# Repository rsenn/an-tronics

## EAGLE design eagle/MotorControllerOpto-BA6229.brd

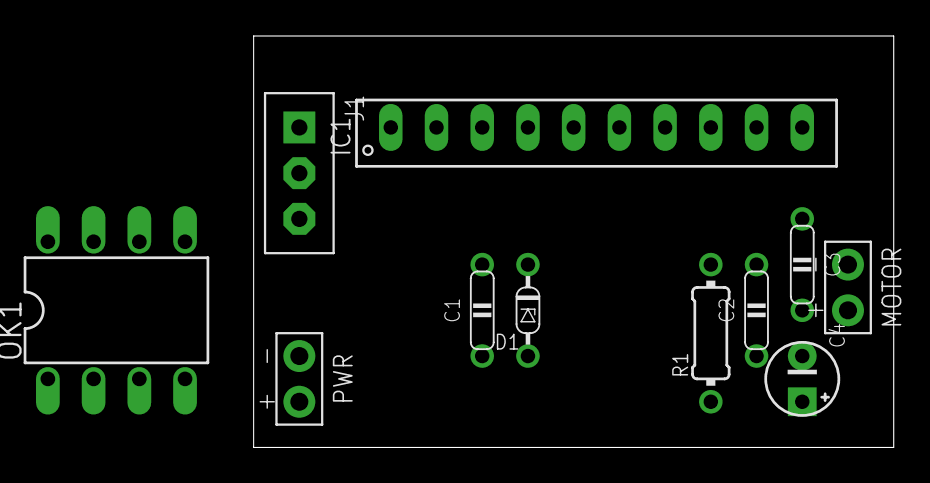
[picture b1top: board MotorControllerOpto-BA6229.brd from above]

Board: 2 copper layers, 35.6 x 22.9 mm, 11 parts (0 on the bottom side), 10 nets, no tracks yet.

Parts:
C1, C2: 0.1μF; C050-020X044
C3: 0.33μF; C050-020X044
C4: 100μF; E2,5-4
D1: Z=4.7V; DO34Z5V
IC1: BA6229; SIL10
J1: CONN-3P-3P; CONN-3P
MOTOR: SPAD+-
OK1: HCPL2730; DIL08
PWR: SPAD+-
R1: 10Ω; 0204/7-V

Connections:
GND: C1.2, C2.2, C4.-, D1.A, IC1.1, J1.1, PWR.1
unnamed: C3.1, IC1.2, MOTOR.2
unnamed: C2.1, IC1.9
unnamed: C1.1, IC1.3
unnamed: D1.C, IC1.4
unnamed: IC1.5, J1.2
unnamed: C3.2, IC1.10, MOTOR.1
unnamed: IC1.6, J1.3
unnamed: IC1.8, R1.1
VCC: C4.+, IC1.7, PWR.2, R1.2

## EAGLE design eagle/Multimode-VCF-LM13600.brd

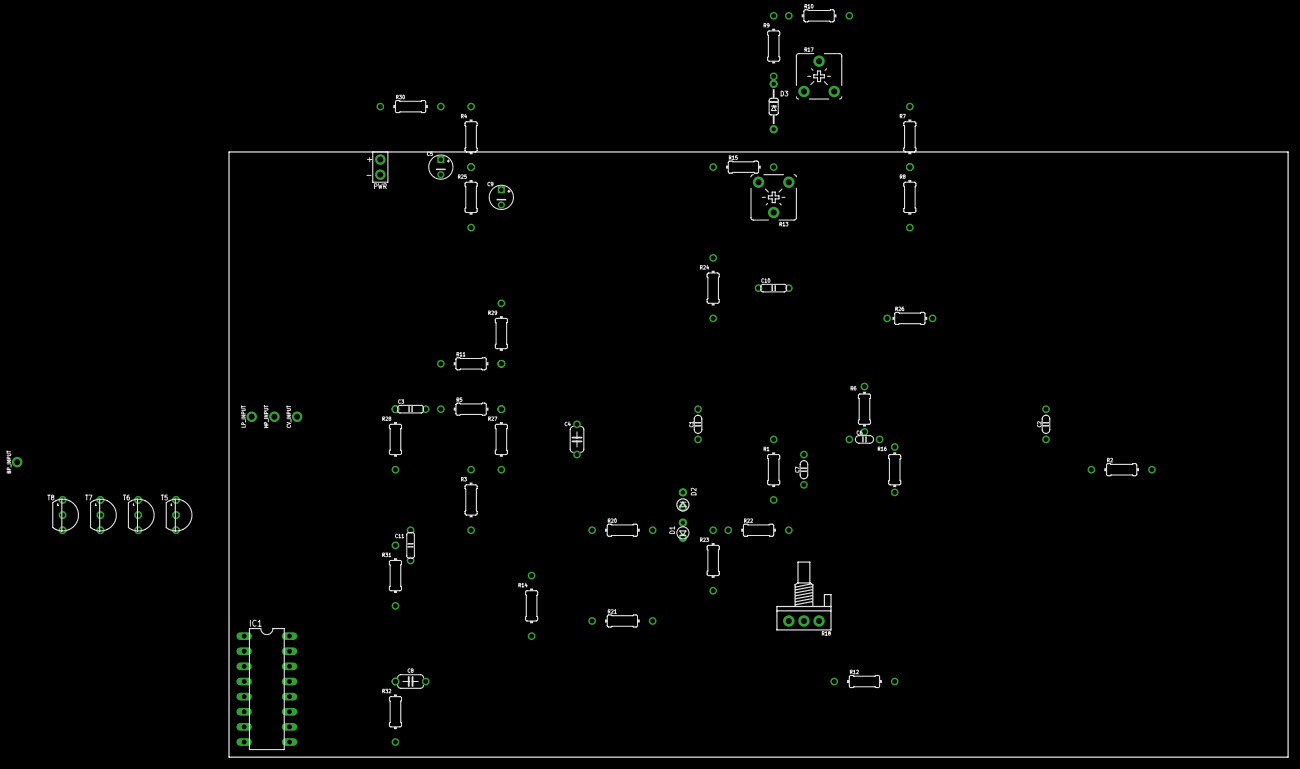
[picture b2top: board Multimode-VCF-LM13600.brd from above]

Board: 2 copper layers, 177.8 x 101.6 mm, 55 parts (0 on the bottom side), 34 nets, no tracks yet.

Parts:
BP_INPUT: SPAD
C1, C2: 220pF; C050-020X036/V
C3, C10: 100nF; C050-020X044
C4: 2.2uF; C050-024X044/V
C5: 33uF; E2.5-4/V
C6: 10pF; C050-020X036
C7: 10uF; C050-020X036/V
C8: 1uF; C050-024X044
C9: 100uF; E2.5-4/V
C11: 100nF; C050-020X044/V
CV_INPUT: SPAD
D1: 1N4148; DO34-2,5-A
D2: 1N4148; DO34-2,5
D3: Z=5.6V/1W; DO35Z7/V
HP_INPUT: SPAD
IC1: LM13600; DIL16
LP_INPUT: SPAD
PWR: SPAD+--+; SPAD-+
R1, R9, R25: 10k; 0204/10-V
R2: 10k; 0204/10
R3, R24: 220k; 0204/10-V
R4: 13k; 0204/10-V
R5: 150k; 0204/10
R6: 100k; 0204/7-V
R7: 18k; 0204/10-V
R8, R14: 22k; 0204/10-V
R10: 4.7k; 0204/10
R11, R12, R15: 100k; 0204/10
R13, R17: 2M; POT-V
R16: 1k; 0204/7-V
R18: 100k; POT
R20: 22k; 0204/10
R21: 30k; 0204/10
R22: 68k; 0204/10
R23, R28, R31, R32: 100k; 0204/10-V
R26: 1k; 0204/7
R27, R29: 1k; 0204/10-V
R30: 100; 0204/10
T5, T6, T7, T8: 2N3904; TO92

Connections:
BIAS: C9.+, R3.1, R4.2, R16.1, R25.1, R26.2, R27.2, R29.1
GND: C2.2, C5.-, C9.-, D3.A, IC1.6, PWR.1, R1.2, R2.1, R8.2, R13.E, R14.2, R18.3, R23.2, R25.2, R28.2, R31.2, R32.2
unnamed: C4.2, R20.1, R21.1
unnamed: IC1.3, R5.2, R24.1, R27.1
unnamed: C1.2, R14.1, T8.1
unnamed: C11.2, R3.2, T8.2
unnamed: C1.1, IC1.5, IC1.7
unnamed: C6.1, C7.1, C10.2, IC1.8, R1.1, R6.1
unnamed: D1.C, D2.A, R20.2
unnamed: D1.A, D2.C, R22.1, R23.1
unnamed: C10.1, R24.2
unnamed: C6.2, IC1.14, R6.2, R16.2
unnamed: R18.2, R21.2
unnamed: C7.2, R18.1, R22.2
unnamed: C4.1, IC1.4, R11.2, R29.2
unnamed: IC1.13, R12.2, R26.1
unnamed: C8.2, R12.1
unnamed: C8.1, LP_INPUT.1, R32.1
unnamed: C11.1, HP_INPUT.1, R31.1
unnamed: C3.2, R5.1
unnamed: BP_INPUT.1, C3.1, R28.1
unnamed: C2.1, IC1.9, IC1.12
unnamed: IC1.10, R2.2, R11.1
unnamed: R17.A, T5.3, T7.2
unnamed: T6.2, T7.1
unnamed: IC1.1, IC1.16, R7.1, T6.1
unnamed: R7.2, R8.1, T5.2
unnamed: D3.C, R9.2, R17.S
unnamed: R10.2, T6.3, T7.3
unnamed: R13.S, T5.1
unnamed: CV_INPUT.1, R15.1
unnamed: R13.A, R15.2
unnamed: PWR.2, R30.1
VCC: C5.+, IC1.11, R4.1, R9.1, R10.1, R30.2, T8.3

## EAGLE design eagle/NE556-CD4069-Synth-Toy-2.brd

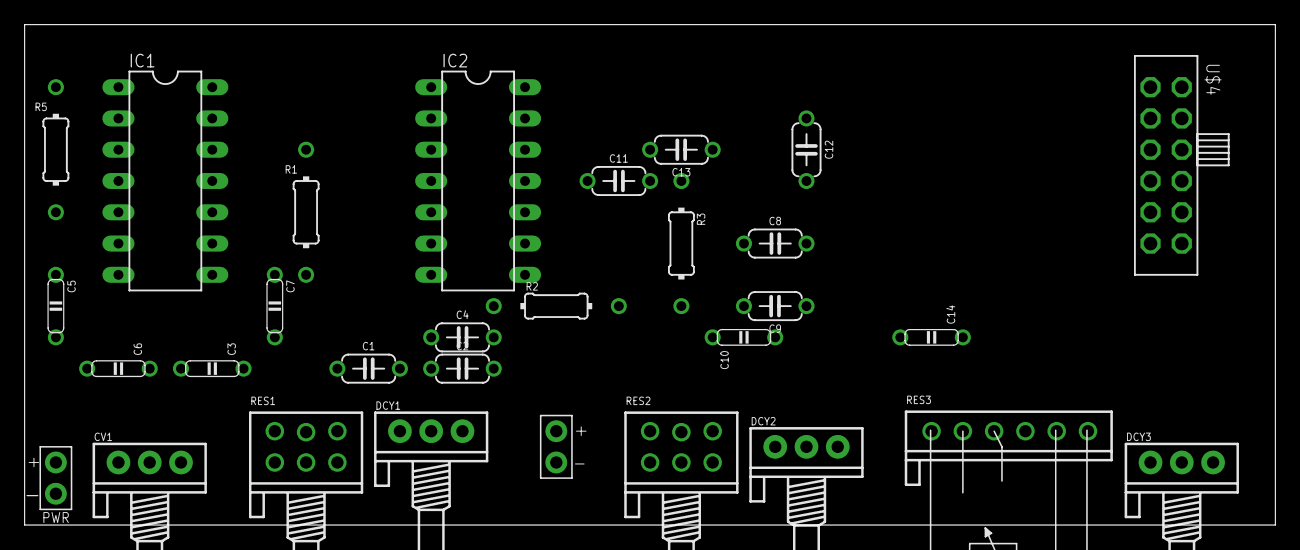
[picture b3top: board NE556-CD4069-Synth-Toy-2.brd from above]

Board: 2 copper layers, 101.6 x 40.6 mm, 30 parts (0 on the bottom side), 22 nets, no tracks yet.

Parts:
C1, C2: 100nF; C050-024X044
C3: 220nF; C050-020X044/V
C4, C11: 470nF; C050-024X044
C5, C7: 100nF; C050-020X044
C6: 10nF; C050-020X044/V
C8, C9: 330nF; C050-024X044
C10, C14: 470nF; C050-020X044/V
C12, C13: 68nF; C050-024X044
CV1: 20kΩ; POT
DCY1, DCY2, DCY3: 20kΩ; POT
IC1: LM556N; DIL14
IC2: 4069N; DIL14
OUT: SPAD+-
R1, R5: 33kΩ; 0204/10-V
R2, R3: R-H0204/10; 0204/10
RES1, RES2: 100kΩ; POT-STEREO-2X3
RES3: 100kΩ; POT-STEREO-1X6-V
S3: VCC_GNDPWR-L; PWR-L
U$4: SL-SW-2P-4T; SLSW-2P4T-2-H

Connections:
GND: C3.2, C5.2, C6.2, C7.2, C10.2, C14.2, CV1.E, DCY1.A, DCY2.A, DCY3.A, IC1.7, IC2.7, OUT.1, S3.1
unnamed: C2.2, IC2.3, IC2.6, RES1.1-E, RES1.1-S
unnamed: IC1.5, R5.2, U$4.A2
unnamed: C4.2, R2.1
unnamed: C3.1, RES1.1-A, RES1.2-E, RES1.2-S
unnamed: C14.1, RES3.1A, RES3.2E, RES3.2S
unnamed: C4.1, IC2.4
unnamed: C1.1, IC2.5, RES1.2-A
unnamed: C5.1, IC1.2, IC1.6, R5.1
unnamed: C6.1, CV1.S, IC1.3, IC1.11
unnamed: C12.1, IC2.13, RES3.2A
unnamed: IC1.9, R1.1, U$4.A3
unnamed: C7.1, IC1.8, IC1.12, R1.2
unnamed: C10.1, RES2.1-A, RES2.2-E, RES2.2-S
unnamed: C8.1, IC2.9, RES2.2-A
unnamed: C13.2, IC2.1, IC2.12, RES3.1E, RES3.1S
unnamed: C11.2, R3.1
unnamed: C11.1, IC2.10
unnamed: OUT.2, R2.2, R3.2
unnamed: C9.2, IC2.8, IC2.11, RES2.1-E, RES2.1-S
TRIG1: C1.2, C2.1, C8.2, C9.1, C12.2, C13.1, DCY1.E, DCY1.S, DCY2.E, DCY2.S, DCY3.E, DCY3.S, U$4.A1, U$4.A6
VCC: CV1.A, IC1.4, IC1.10, IC1.14, IC2.14, S3.2

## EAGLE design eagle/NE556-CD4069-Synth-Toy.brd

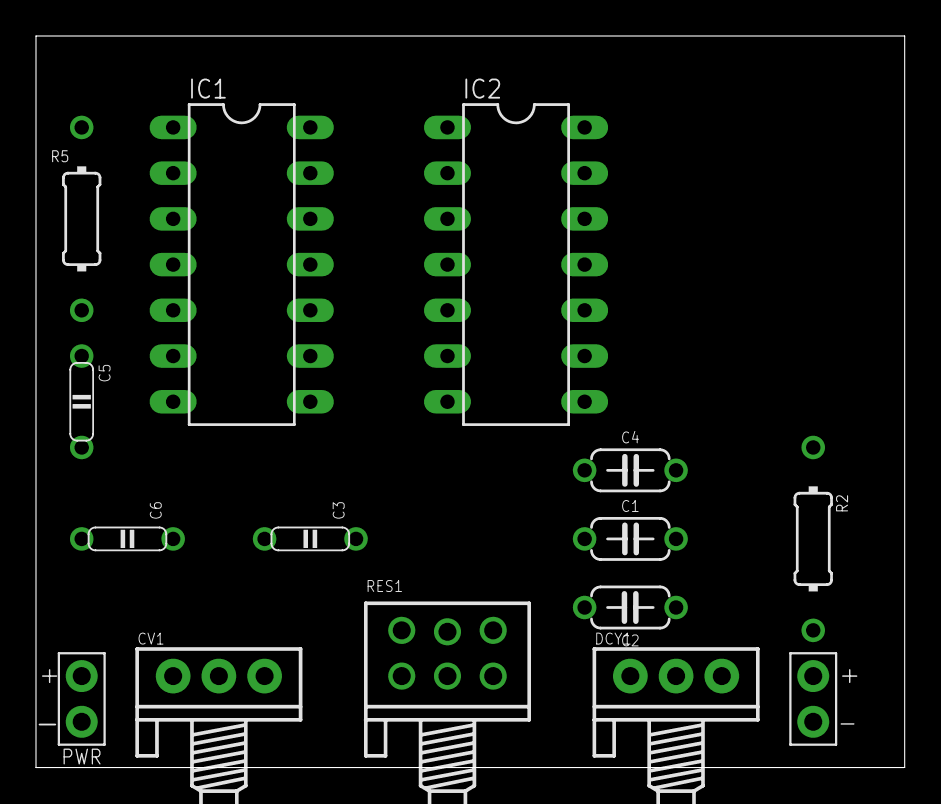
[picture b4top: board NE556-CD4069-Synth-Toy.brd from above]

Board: 2 copper layers, 48.3 x 40.6 mm, 15 parts (0 on the bottom side), 12 nets, no tracks yet.

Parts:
C1, C2: 100nF; C050-024X044
C3: 220nF; C050-020X044/V
C4: 470nF; C050-024X044
C5: 100nF; C050-020X044
C6: 10nF; C050-020X044/V
CV1: 20kΩ; POT
DCY1: 20kΩ; POT
IC1: LM556N; DIL14
IC2: 4069N; DIL14
OUT: SPAD+-
R2: R-H0204/10; 0204/10
R5: R-H0204/10-V; 0204/10-V
RES1: 100kΩ; POT-STEREO-2X3
S3: VCC_GNDPWR-L; PWR-L

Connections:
GND: C3.2, C5.2, C6.2, CV1.E, DCY1.A, IC1.7, IC2.7, OUT.1, S3.1
unnamed: C2.2, IC2.6, IC2.9, RES1.1-E, RES1.1-S
unnamed: IC1.5, R5.2
unnamed: C4.2, R2.1
unnamed: C3.1, RES1.1-A, RES1.2-E, RES1.2-S
unnamed: C1.2, C2.1, DCY1.E, DCY1.S
unnamed: C4.1, IC2.8
unnamed: C1.1, IC2.5, RES1.2-A
unnamed: C5.1, IC1.2, IC1.6, R5.1
unnamed: C6.1, CV1.S, IC1.3
unnamed: OUT.2, R2.2
VCC: CV1.A, IC1.4, IC1.14, IC2.14, S3.2

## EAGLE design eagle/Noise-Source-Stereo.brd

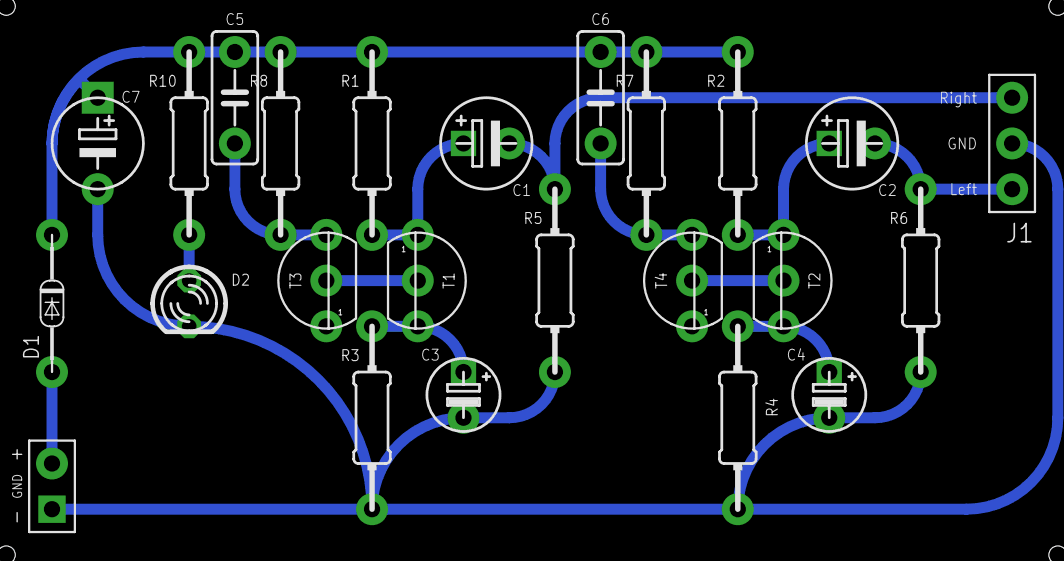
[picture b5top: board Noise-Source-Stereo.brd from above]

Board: 2 copper layers, 24 parts (0 on the bottom side), 14 nets.

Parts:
C1, C2: 10µF; E2,5-5
C3, C4: 10µF; E2.5-4/V
C5, C6: 100nF; C050-025X075/V
C7: 470µF; E5-5/V
D1: 1N4002; DO34-7
D2: LED-3MM/V; LED_3MM/V
GND: VCC_GNDL; SPAD-+
J1: SAUDIOR-GND-L; SPAD-R-GND-L
R1, R2: 4.7kΩ; 0204/10-V
R3: 1kΩ; 0204/10-V
R4: 1kΩ; 0204/10
R5, R6: 100kΩ; 0204/10-V
R7, R8: 680kΩ; 0204/10-V
R10: 15kΩ; 0204/10-V
T1, T2, T3, T4: BC547; TO92

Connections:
GND: C3.-, C4.-, C7.-, D2.K, GND.1, J1.0, R3.2, R4.2, R5.2, R6.2
unnamed: C2.+, R2.2, T2.1
unnamed: C4.+, R4.1, T2.3
unnamed: C3.+, R3.1, T1.3
unnamed: C1.+, R1.2, T1.1
unnamed: T1.2, T3.2
unnamed: C5.2, R8.2, T3.3
unnamed: T2.2, T4.2
unnamed: D2.A, R10.2
unnamed: C6.2, R7.2, T4.3
unnamed: C2.-, J1.L, R6.1
unnamed: C1.-, J1.R, R5.1
VCC: D1.A, GND.2
VCC2: C5.1, C6.1, C7.+, D1.C, R1.1, R2.1, R7.1, R8.1, R10.1

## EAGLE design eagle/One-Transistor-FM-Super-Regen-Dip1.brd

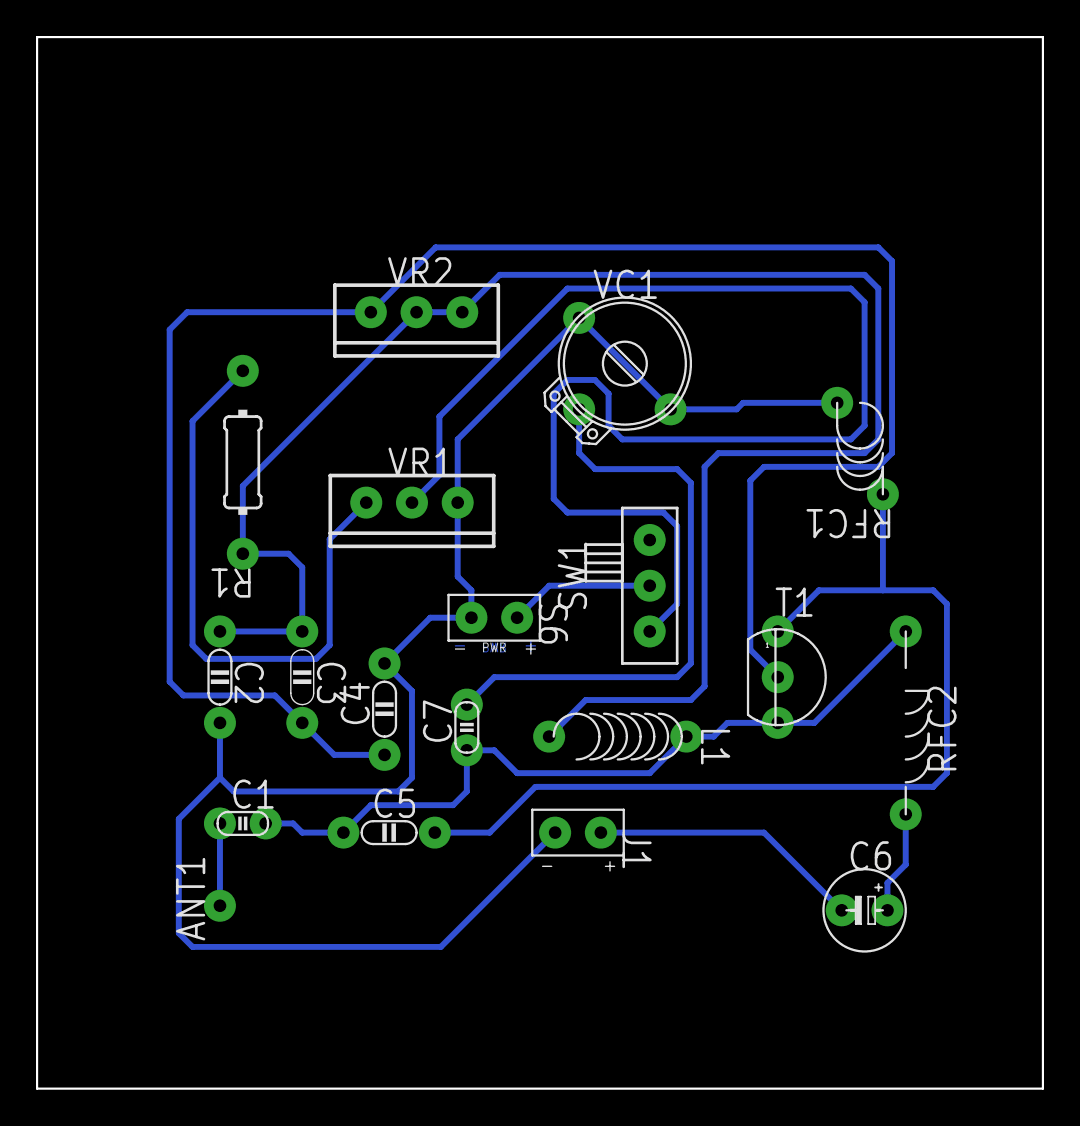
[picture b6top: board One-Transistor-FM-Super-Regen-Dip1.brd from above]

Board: 2 copper layers, 55.9 x 58.4 mm, 19 parts (0 on the bottom side), 12 nets.

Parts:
ANT1: ANT; SPAD
C1: 5pF; C025-015X024
C2: 0.001; C050-020X036/V
C3: 0.001; C050-020X036
C4: 100pF; C050-020X036/V
C5: 10pF; C050-020X036/V
C6: 10µF; E2,5-4
C7: 47pF; C025-015X024
J1: SPAD+-+-; SPAD+-
L1: 4t; L-04/7-V
R1: 2.2kΩ; 0204/10-V
RFC1: 10µH; L-04-2/5V
RFC2: 10µH; L-03/10
S6: VCC_GNDPWR-R; PWR-R
SW1: SW-SPST-SL-1P2T-H; SLSW-1P2T-H
T1: 2N3904; TO92
VC1: 20pF; TRIM-2222-808
VR1: 10kΩ; TRIM-POT
VR2: 100kΩ; TRIM-POT

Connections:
GND: C2.2, C4.2, J1.1, RFC1.1, S6.1, VC1.1, VC1.3, VR1.E
unnamed: ANT1.1, C1.1
unnamed: C1.2, C5.1, C7.1, L1.1, RFC2.2, T1.3
unnamed: C2.1, C3.1, L1.2, R1.1, VR2.E, VR2.S
unnamed: C7.2, VC1.2
unnamed: R1.2, VR1.A
unnamed: C5.2, RFC1.2, T1.1
unnamed: C3.2, C4.1, T1.2, VR2.A
unnamed: SW1.S, VR1.S
unnamed: C6.+, RFC2.1
unnamed: C6.-, J1.2
VCC: S6.2, SW1.P

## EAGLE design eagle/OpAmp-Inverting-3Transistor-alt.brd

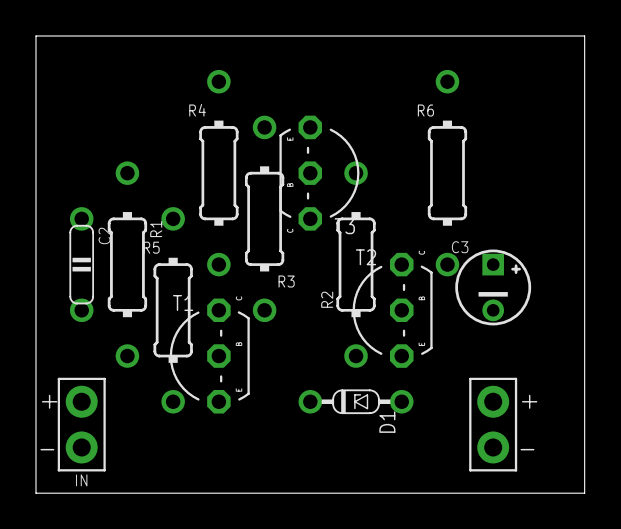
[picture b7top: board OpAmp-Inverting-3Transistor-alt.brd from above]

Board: 2 copper layers, 30.5 x 25.4 mm, 14 parts (0 on the bottom side), 11 nets, no tracks yet.

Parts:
C2: 33nF; C050-020X044
C3: 3.3μF; E2.5-4/V
D1: Z=3.3V; DO34Z5V
IN: SPAD-+
OUT: SPAD+-
R1: 100kΩ; 0204/10
R2: 1MΩ; 0204/10
R3: 75kΩ; 0204/10-V
R4: 7.5kΩ; 0204/10-V
R5: 4.7kΩ; 0204/10-V
R6: 1kΩ; 0204/10-V
T1, T2: 2N3904; TO92-EBC
T3: 2N3906; TO92-EBC

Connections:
9V: R4.1, R5.1, R6.1, T3.E
GND: D1.A, IN.1, OUT.1, T2.E
unnamed: D1.C, R5.2, T1.E
unnamed: R3.1, R4.2, T1.C
unnamed: T2.B, T3.C
unnamed: C2.2, IN.2
unnamed: C2.1, R1.1
unnamed: R1.2, R2.1, T1.B
unnamed: R3.2, T3.B
unnamed: C3.+, R2.2, R6.2, T2.C
unnamed: C3.-, OUT.2
